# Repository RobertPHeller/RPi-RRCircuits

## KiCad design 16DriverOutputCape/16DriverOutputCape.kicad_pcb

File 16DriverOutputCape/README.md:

# 16DriverOutputCape

This is a MCP23017 with two octal buffers meant to drive 16 LEDs (such as 
signal lamps). No PWM or special effects.  This board is a Cape for a 
BeagleBone Black or Green.  Has address jumpers for the MCP23017 and can be 
stacked -- up to 8 of these capes for up to 128 LEDS -- each board has power 
terminals for the LEDs.

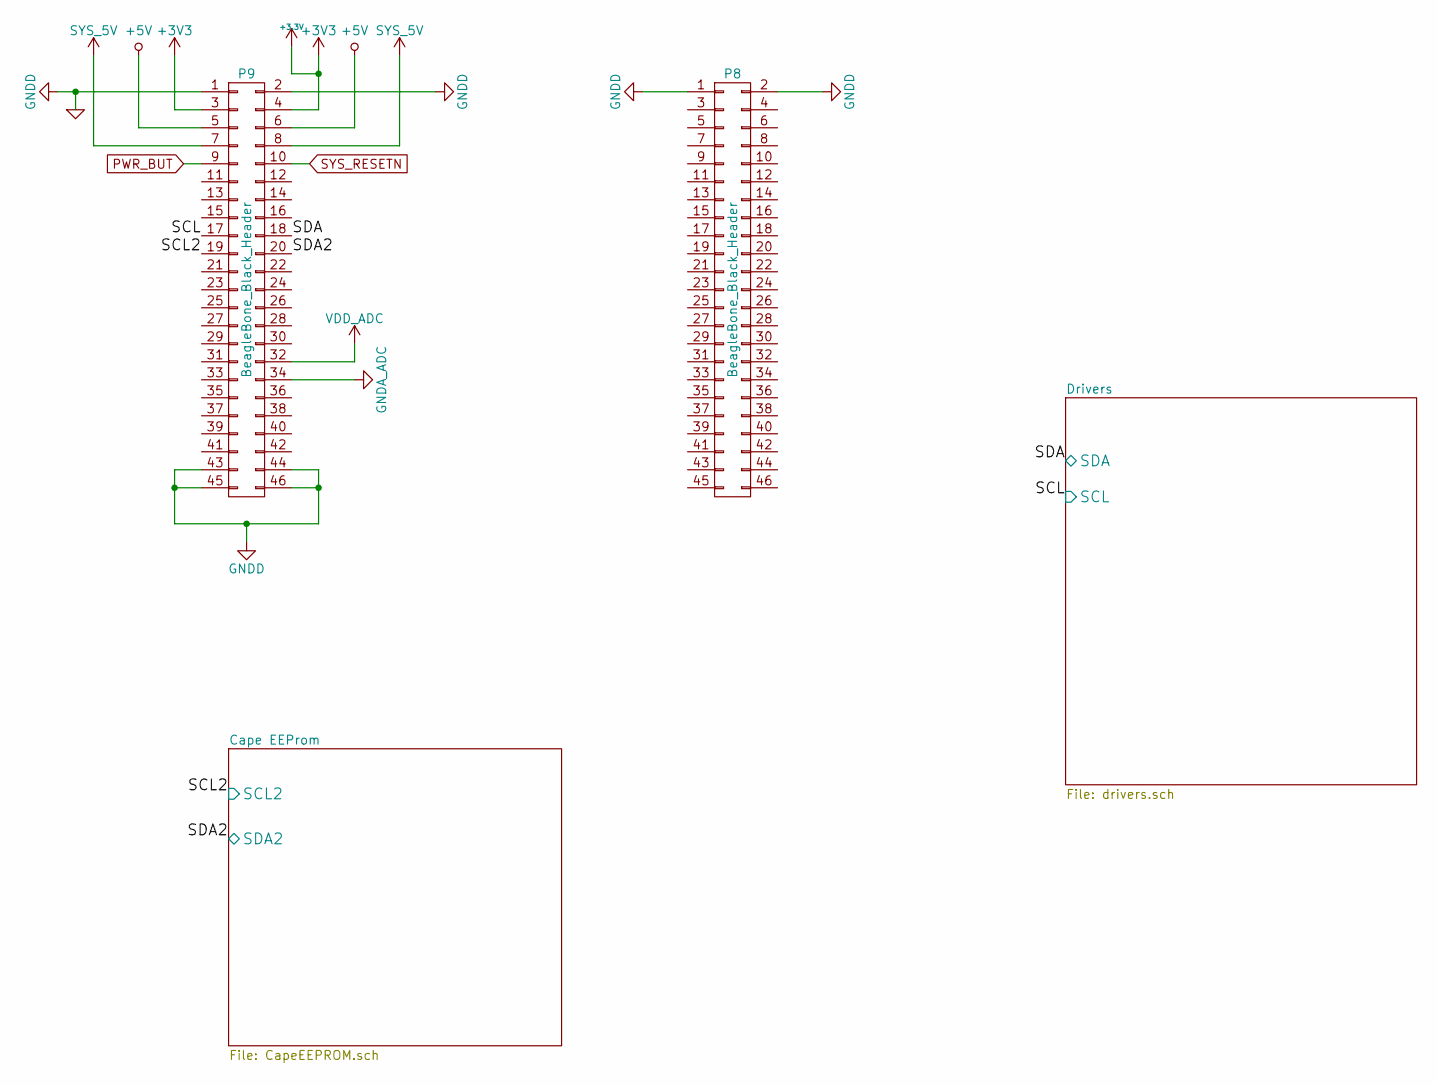
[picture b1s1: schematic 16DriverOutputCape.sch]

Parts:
P8, P9: BeagleBone_Black_Header; Socket_BeagleBone_Black

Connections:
+3.3V: P9.3, P9.4; also elsewhere on the board
+5V: P9.5, P9.6
/Cape EEProm/SCL2: P9.19; also elsewhere on the board
/Cape EEProm/SDA2: P9.20; also elsewhere on the board
/Drivers/SCL: P9.17; also elsewhere on the board
/Drivers/SDA: P9.18; also elsewhere on the board
GND: P8.1, P8.2, P9.1, P9.2, P9.43, P9.44, P9.45, P9.46; also elsewhere on the board
SYS_5V: P9.7, P9.8

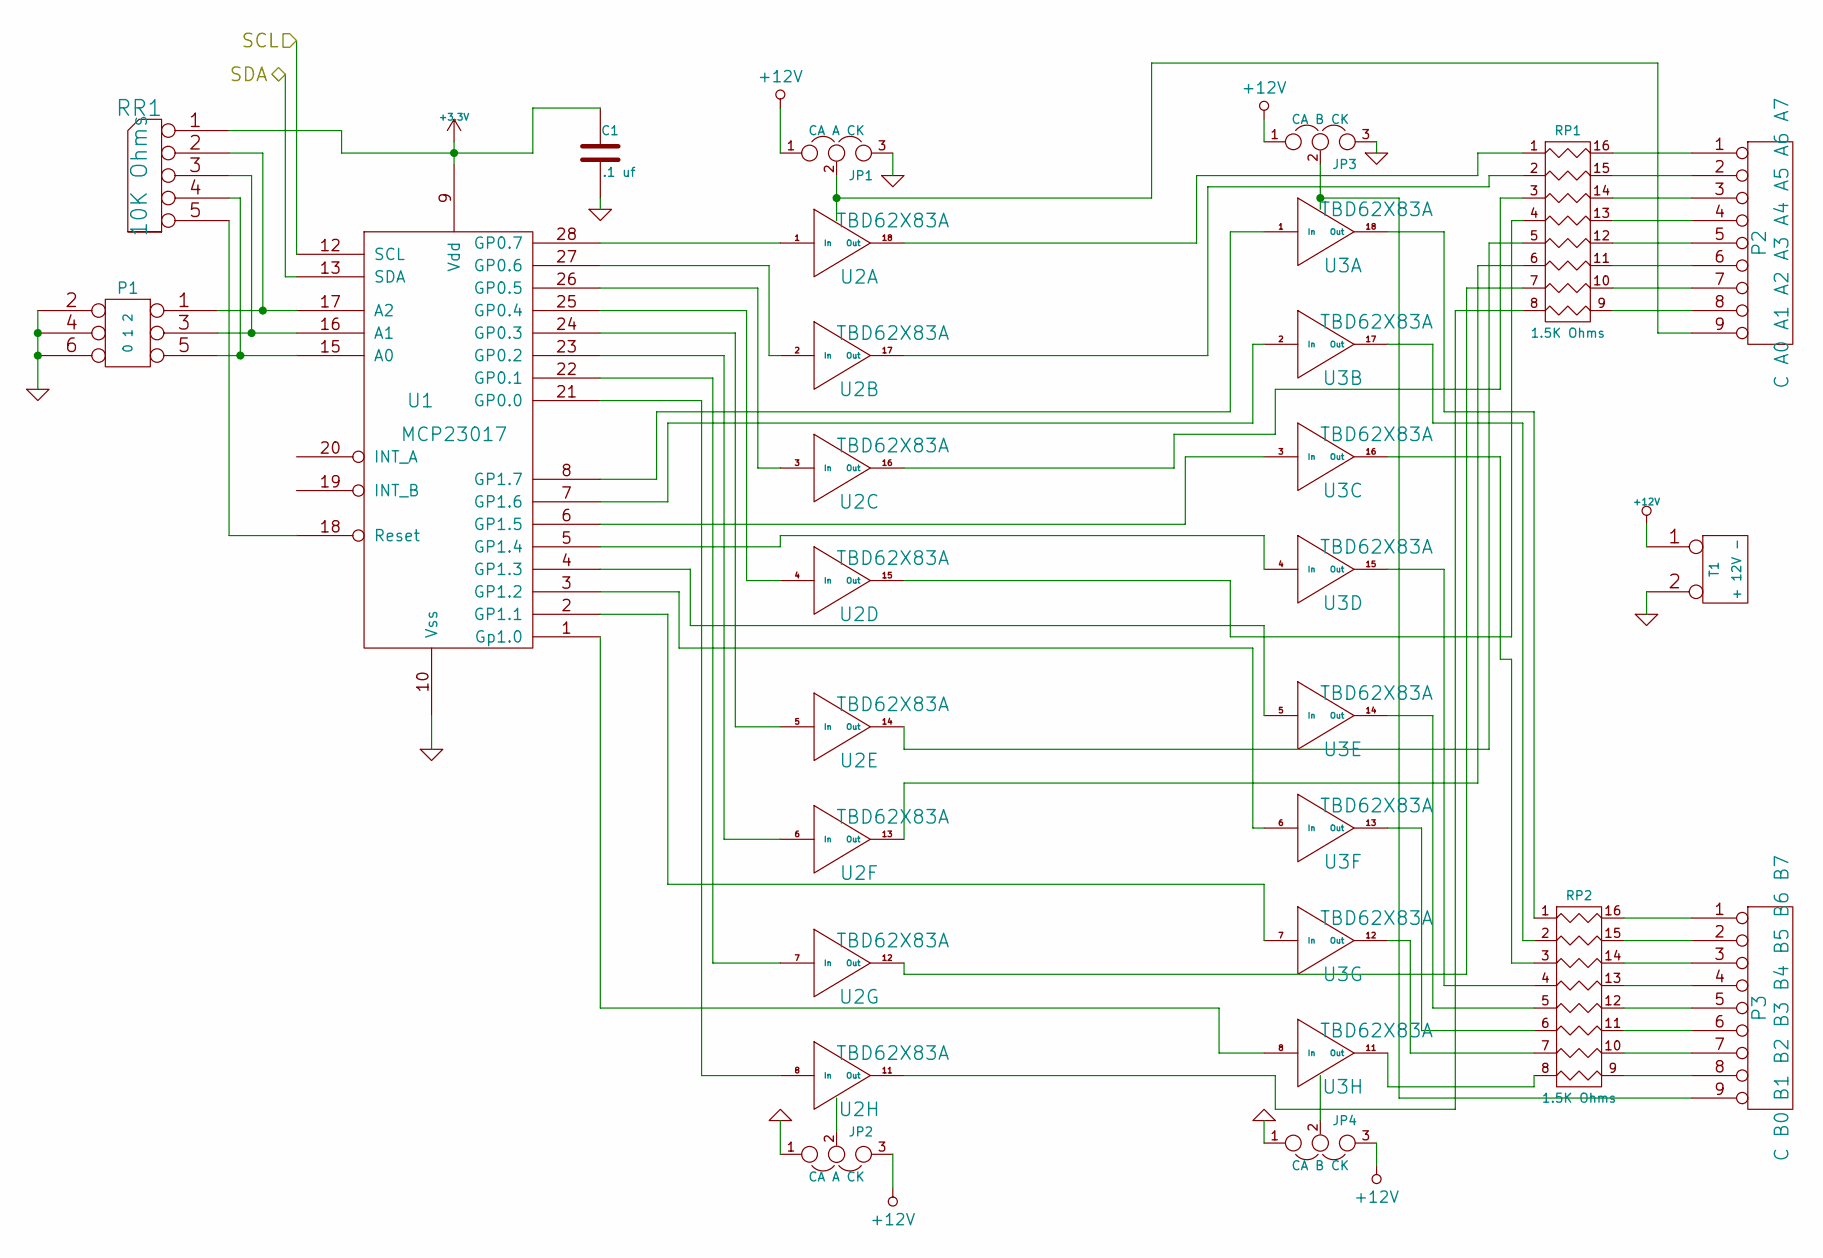
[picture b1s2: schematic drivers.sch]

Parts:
C1: .1 uf
JP1, JP2: CA A CK
JP3, JP4: CA B CK
P1: 0 1 2
P2: C A0 A1 A2 A3 A4 A5 A6 A7
P3: C B0 B1 B2 B3 B4 B5 B6 B7
RP1, RP2: 1.5K Ohms
RR1: 10K Ohms
T1: + 12V -
U1: MCP23017
U2, U3: TBD62X83A

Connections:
+3.3V: C1.1, RR1.1 (COM), U1.9 (Vdd); also elsewhere on the board
+12V: JP1.1, JP2.3, JP3.1, JP4.3, T1.1
/Drivers/SCL: U1.12 (SCL); also elsewhere on the board
/Drivers/SDA: U1.13 (SDA); also elsewhere on the board
GND: C1.2, JP1.3, JP2.1, JP3.3, JP4.1, P1.2, P1.4, P1.6, T1.2 (PM), U1.10 (Vss); also elsewhere on the board
unnamed: P1.1, RR1.2, U1.17 (A2)
unnamed: P1.3, RR1.3, U1.16 (A1)
unnamed: P1.5, RR1.4, U1.15 (A0)
unnamed: RR1.5, U1.18 (Reset)
unnamed: JP2.2, U2.9 (IC)
unnamed: JP3.2, P3.9, U3.10 (OC)
unnamed: JP1.2, P2.9, U2.10 (OC)
unnamed: JP4.2, U3.9 (IC)
unnamed: RP2.6, U3.13 (Out)
unnamed: RP2.8, U3.11 (Out)
unnamed: RP2.7, U3.12 (Out)
unnamed: RP2.5, U3.14 (Out)
unnamed: RP2.4, U3.15 (Out)
unnamed: RP2.3, U3.16 (Out)
unnamed: U1.26 (GP0.5), U2.3 (In)
unnamed: U1.28 (GP0.7), U2.1 (In)
unnamed: U1.27 (GP0.6), U2.2 (In)
unnamed: U1.25 (GP0.4), U2.4 (In)
unnamed: U1.24 (GP0.3), U2.5 (In)
unnamed: RP1.5, U2.14 (Out)
unnamed: U1.23 (GP0.2), U2.6 (In)
unnamed: U1.5 (GP1.4), U3.4 (In)
unnamed: U1.8 (GP1.7), U3.1 (In)
unnamed: U1.22 (GP0.1), U2.7 (In)
unnamed: RP1.7, U2.12 (Out)
unnamed: RP2.1, U3.18 (Out)
unnamed: U1.7 (GP1.6), U3.2 (In)
unnamed: P3.1, RP2.16 (R1)
unnamed: P3.2, RP2.15 (R2)
unnamed: P3.3, RP2.14 (R3)
unnamed: P3.4, RP2.13 (R4)
unnamed: P3.5, RP2.12 (R5)
unnamed: P3.6, RP2.11 (R6)
unnamed: P3.7, RP2.10 (R7)
unnamed: U1.21 (GP0.0), U2.8 (In)
unnamed: P3.8, RP2.9 (R8)
unnamed: U1.1 (Gp1.0), U3.8 (In)
unnamed: U1.2 (GP1.1), U3.7 (In)
unnamed: U1.3 (GP1.2), U3.6 (In)
unnamed: U1.4 (GP1.3), U3.5 (In)
unnamed: P2.6, RP1.11 (R6)
unnamed: RP2.2, U3.17 (Out)
unnamed: P2.1, RP1.16 (R1)
unnamed: P2.2, RP1.15 (R2)
unnamed: P2.3, RP1.14 (R3)
unnamed: P2.4, RP1.13 (R4)
unnamed: P2.5, RP1.12 (R5)
unnamed: P2.7, RP1.10 (R7)
unnamed: P2.8, RP1.9 (R8)
unnamed: RP1.8, U2.11 (Out)
unnamed: RP1.6, U2.13 (Out)
unnamed: RP1.4, U2.15 (Out)
unnamed: RP1.3, U2.16 (Out)
unnamed: RP1.2, U2.17 (Out)
unnamed: RP1.1, U2.18 (Out)
unnamed: U1.6 (GP1.5), U3.3 (In)

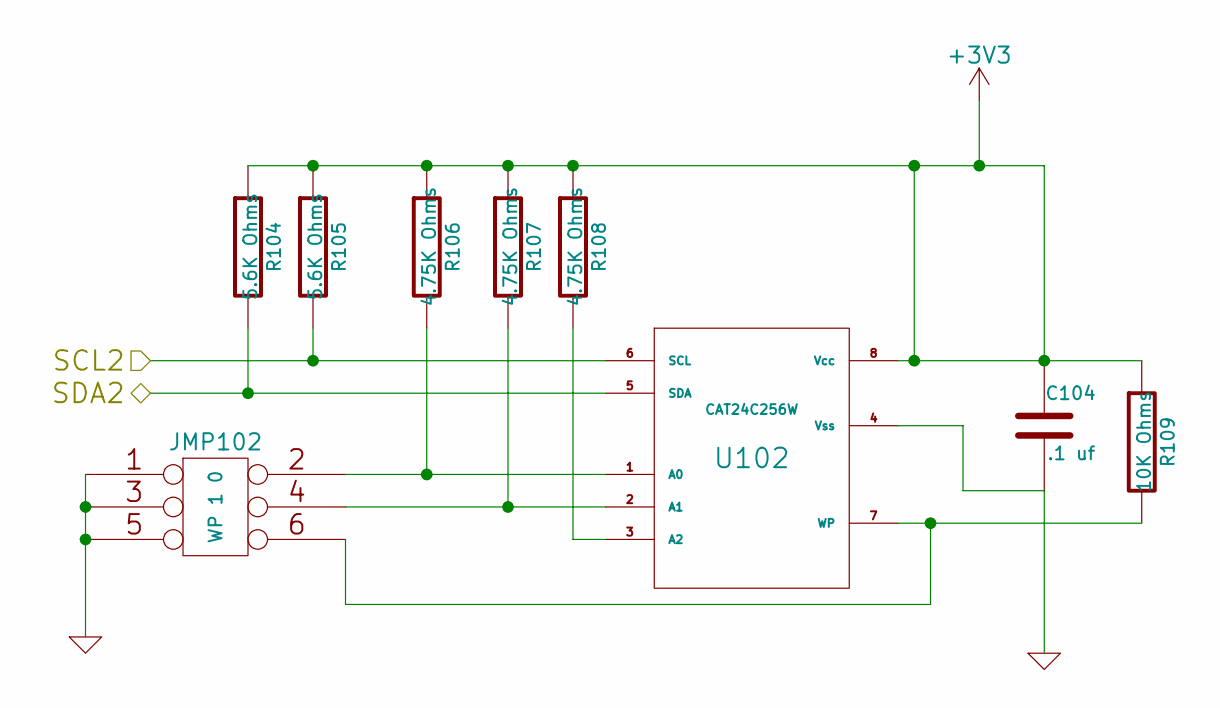
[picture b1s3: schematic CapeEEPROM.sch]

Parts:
C104: .1 uf
JMP102: WP 1 0
R104, R105: 5.6K Ohms
R106, R107, R108: 4.75K Ohms
R109: 10K Ohms
U102: CAT24C256W

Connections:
+3.3V: C104.1, R104.1, R105.1, R106.1, R107.1, R108.1, R109.1, U102.8 (Vcc); also elsewhere on the board
/Cape EEProm/SCL2: R105.2, U102.6 (SCL); also elsewhere on the board
/Cape EEProm/SDA2: R104.2, U102.5 (SDA); also elsewhere on the board
GND: C104.2, JMP102.1, JMP102.3, JMP102.5, U102.4 (Vss); also elsewhere on the board
unnamed: R108.2, U102.3 (A2)
unnamed: JMP102.4, R107.2, U102.2 (A1)
unnamed: JMP102.2, R106.2, U102.1 (A0)
unnamed: JMP102.6, R109.2, U102.7 (WP)

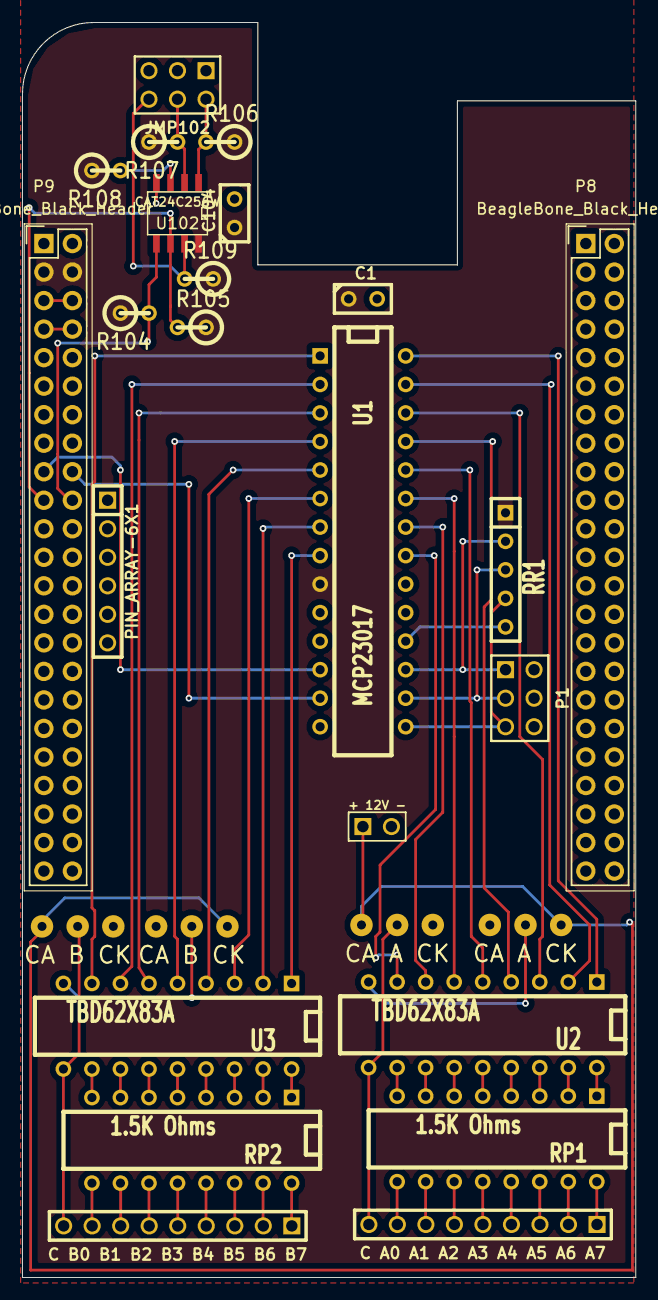
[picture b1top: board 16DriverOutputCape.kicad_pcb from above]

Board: 2 copper layers, 54.6 x 111.8 mm, 27 parts (0 on the bottom side), 69 nets.

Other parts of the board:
PIN_ARRAY-6X1: Val**; PIN_ARRAY-6X1

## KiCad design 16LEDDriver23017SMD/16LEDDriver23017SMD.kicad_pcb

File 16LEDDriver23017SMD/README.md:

# 16LEDDriver23017SMD

This is a SMD variant of 16DriverOutputHAT.

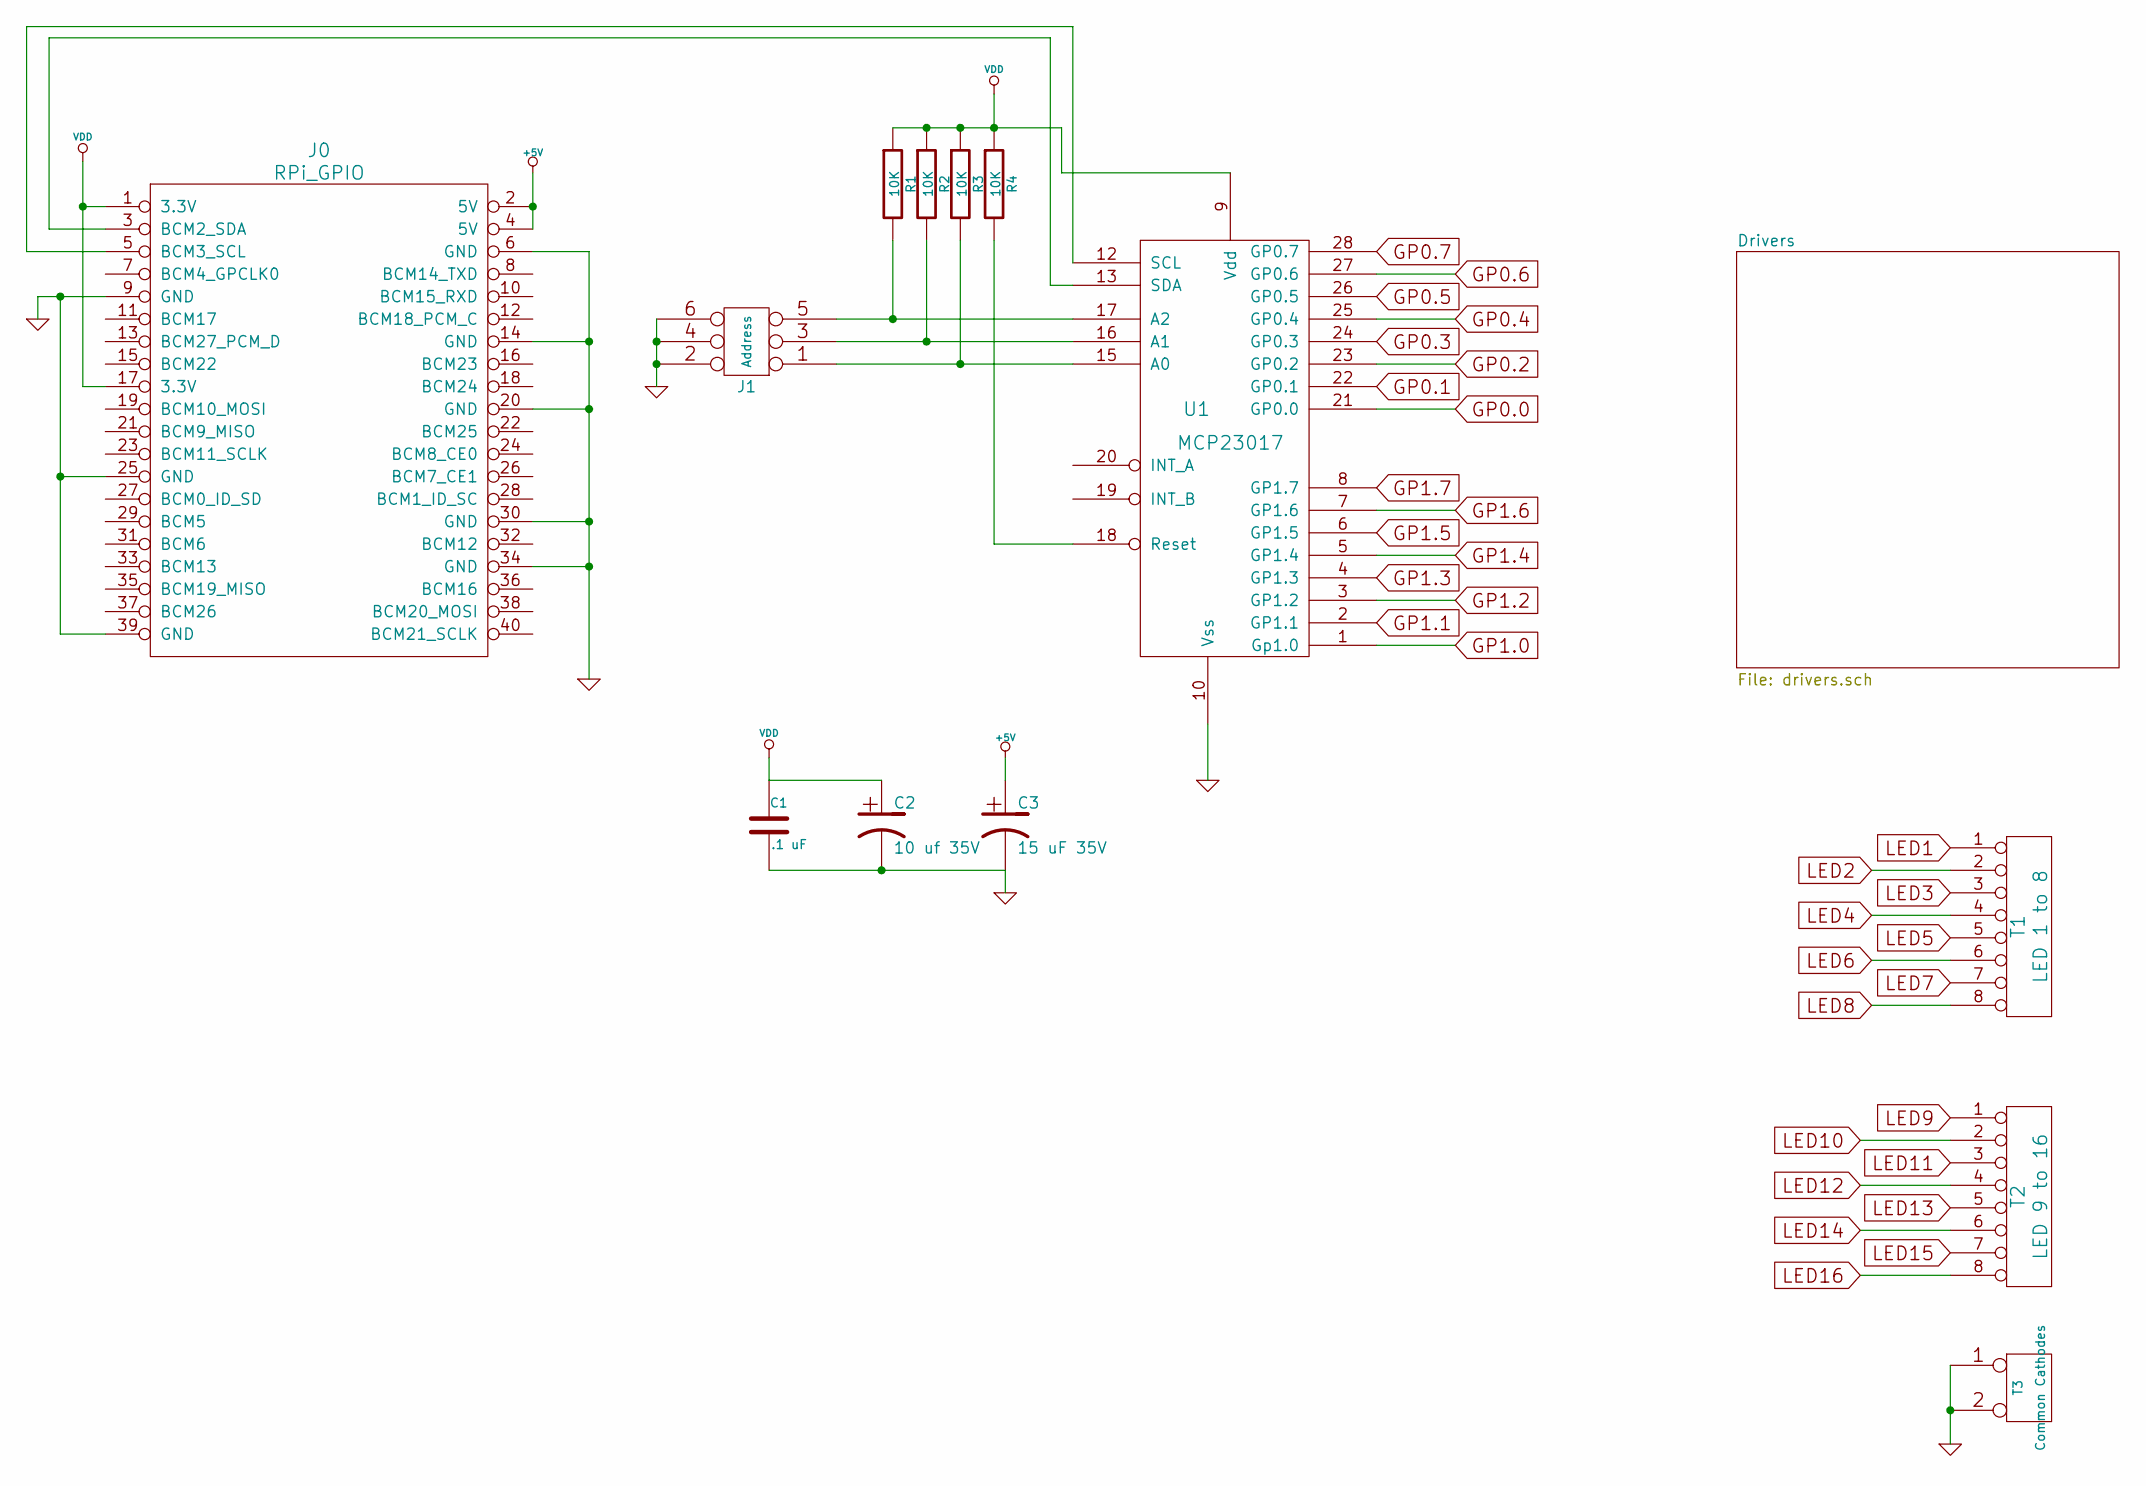
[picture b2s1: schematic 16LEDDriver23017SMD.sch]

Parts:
C1: .1 uF
C2: 10 uf 35V
C3: 15 uF 35V
J0: RPi_GPIO; Samtec_HLE-120-02-XXX-DV-BE-XX-XX
J1: Address; pin_array_3x2
R1, R2, R3, R4: 10K
T1: LED 1 to 8
T2: LED 9 to 16
T3: Common Cathodes
U1: MCP23017; SOIC-28

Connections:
+5V: C3.1, J0.2 (5V), J0.4 (5V); also elsewhere on the board
GND: C1.2, C2.2, C3.2, J0.6 (GND), J0.9 (GND), J0.14 (GND), J0.20 (GND), J0.25 (GND), J0.30 (GND), J0.34 (GND), J0.39 (GND), J1.2, J1.4, J1.6, T3.1, T3.2 (PM), U1.10 (Vss); also elsewhere on the board
GP0.0: U1.21 (GP0.0); also elsewhere on the board
GP0.1: U1.22 (GP0.1); also elsewhere on the board
GP0.2: U1.23 (GP0.2); also elsewhere on the board
GP0.3: U1.24 (GP0.3); also elsewhere on the board
GP0.4: U1.25 (GP0.4); also elsewhere on the board
GP0.5: U1.26 (GP0.5); also elsewhere on the board
GP0.6: U1.27 (GP0.6); also elsewhere on the board
GP0.7: U1.28 (GP0.7); also elsewhere on the board
GP1.0: U1.1 (Gp1.0); also elsewhere on the board
GP1.1: U1.2 (GP1.1); also elsewhere on the board
GP1.2: U1.3 (GP1.2); also elsewhere on the board
GP1.3: U1.4 (GP1.3); also elsewhere on the board
GP1.4: U1.5 (GP1.4); also elsewhere on the board
GP1.5: U1.6 (GP1.5); also elsewhere on the board
GP1.6: U1.7 (GP1.6); also elsewhere on the board
GP1.7: U1.8 (GP1.7); also elsewhere on the board
LED1: T1.1; also elsewhere on the board
LED2: T1.2; also elsewhere on the board
LED3: T1.3; also elsewhere on the board
LED4: T1.4; also elsewhere on the board
LED5: T1.5; also elsewhere on the board
LED6: T1.6; also elsewhere on the board
LED7: T1.7; also elsewhere on the board
LED8: T1.8; also elsewhere on the board
LED9: T2.1; also elsewhere on the board
LED10: T2.2; also elsewhere on the board
LED11: T2.3; also elsewhere on the board
LED12: T2.4; also elsewhere on the board
LED13: T2.5; also elsewhere on the board
LED14: T2.6; also elsewhere on the board
LED15: T2.7; also elsewhere on the board
LED16: T2.8; also elsewhere on the board
unnamed: J0.5 (BCM3_SCL), U1.12 (SCL)
unnamed: J0.3 (BCM2_SDA), U1.13 (SDA)
unnamed: J1.5, R1.2, U1.17 (A2)
unnamed: J1.3, R2.2, U1.16 (A1)
unnamed: J1.1, R3.2, U1.15 (A0)
unnamed: R4.2, U1.18 (Reset)
VDD: C1.1, C2.1, J0.1 (3.3V), J0.17 (3.3V), R1.1, R2.1, R3.1, R4.1, U1.9 (Vdd)

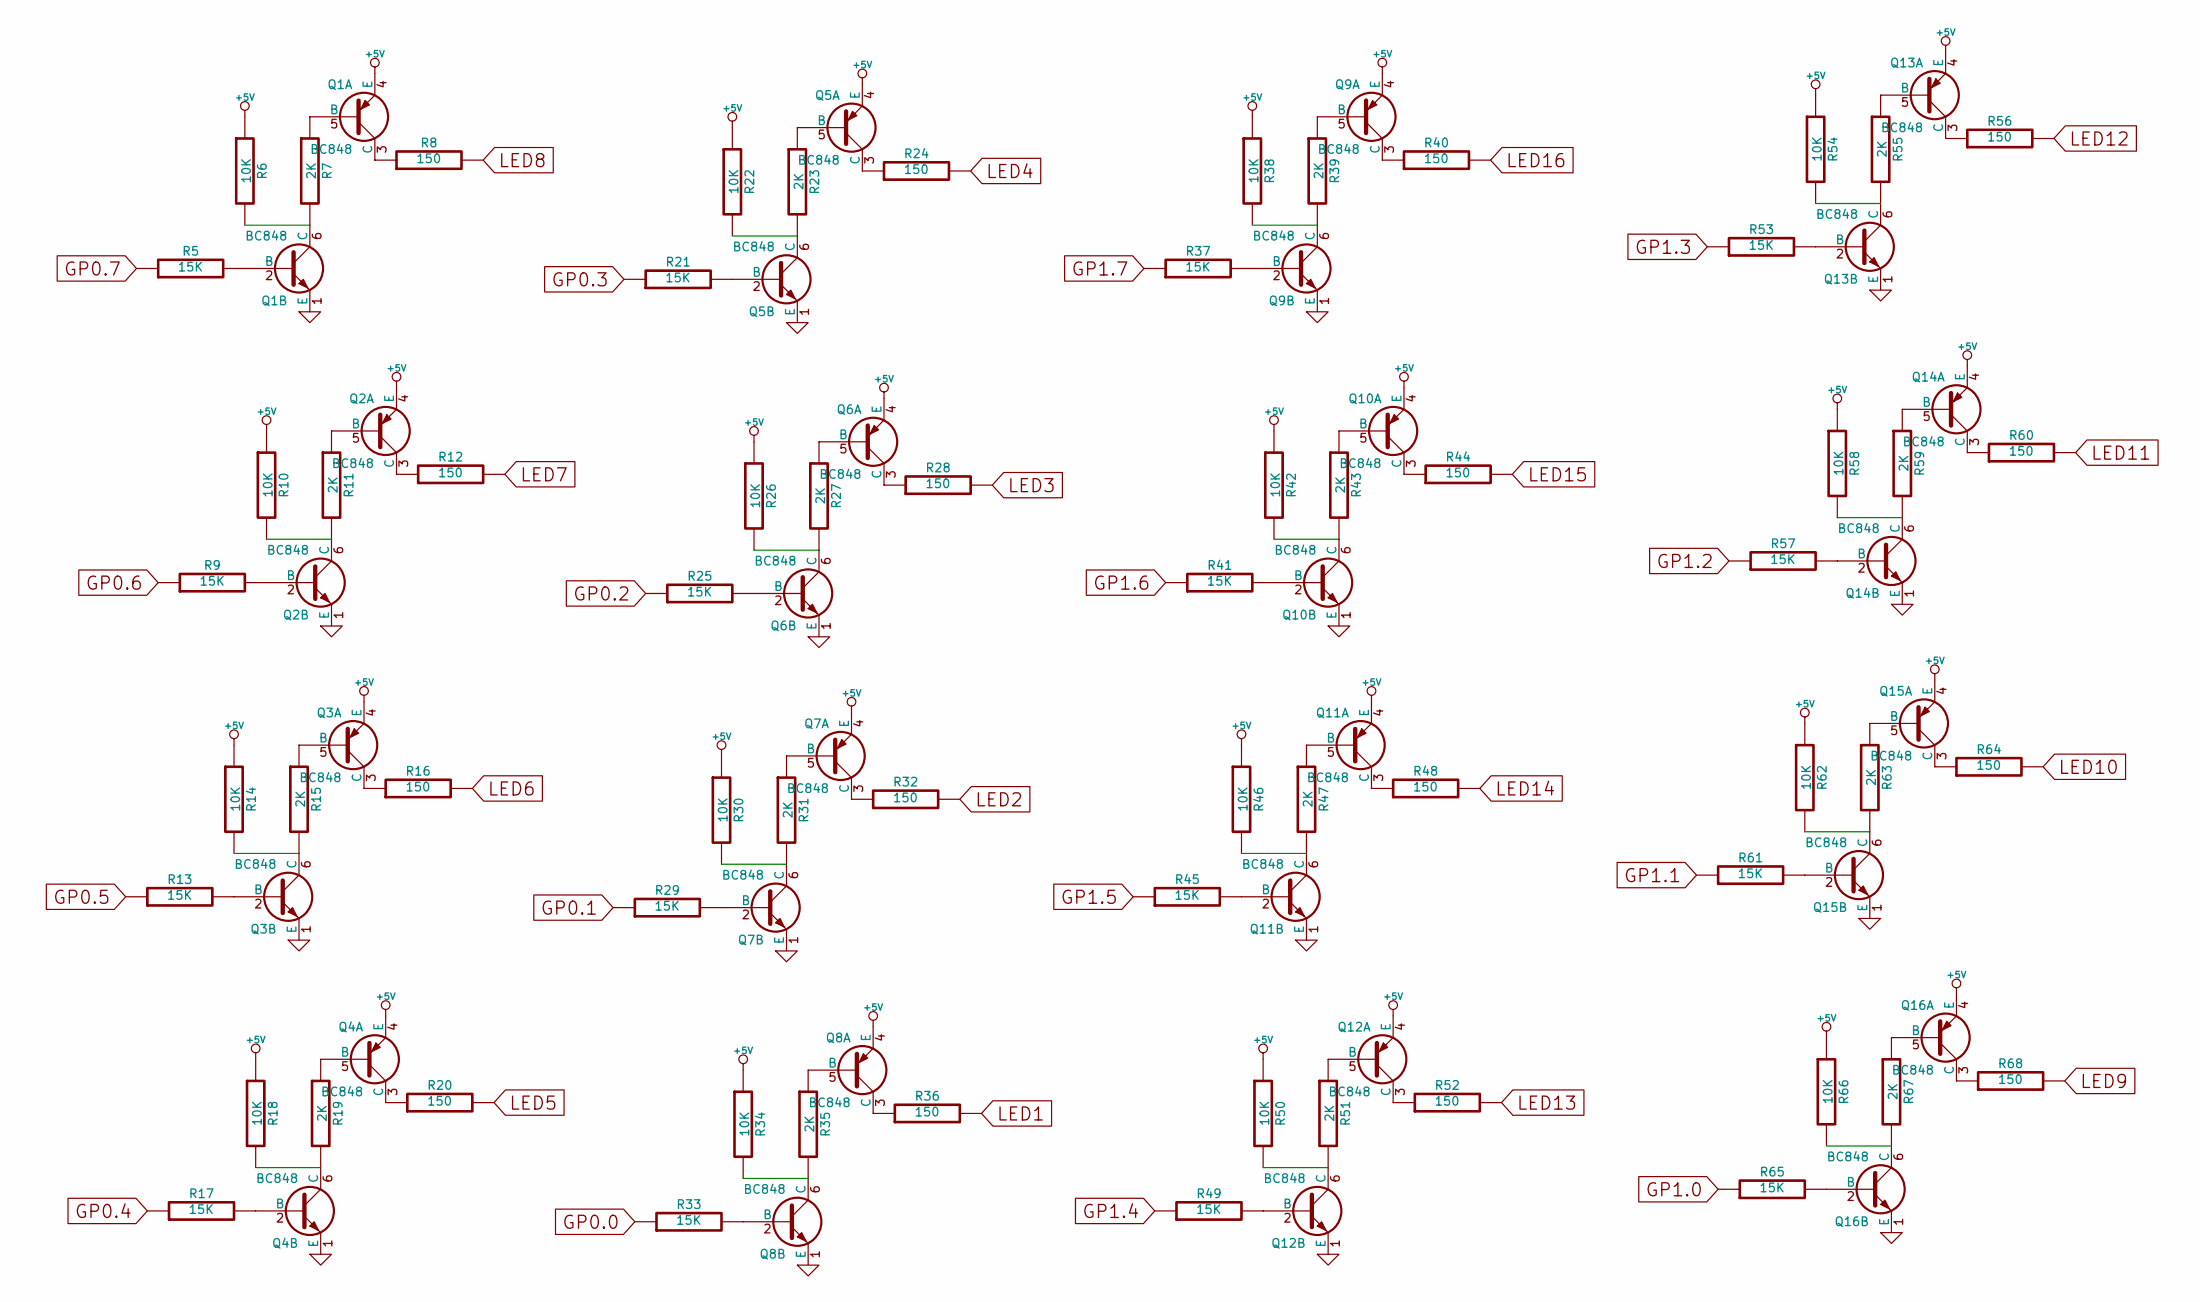
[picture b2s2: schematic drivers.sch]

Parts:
Q1, Q2, Q3, Q4, Q5, Q6, Q7, Q8, Q9, Q10, Q11, Q12, Q13, Q14, Q15, Q16: BC848; SOT-363
R5, R9, R13, R17, R21, R25, R29, R33, R37, R41, R45, R49, R53, R57, R61, R65: 15K
R6, R10, R14, R18, R22, R26, R30, R34, R38, R42, R46, R50, R54, R58, R62, R66: 10K
R7, R11, R15, R19, R23, R27, R31, R35, R39, R43, R47, R51, R55, R59, R63, R67: 2K
R8, R12, R16, R20, R24, R28, R32, R36, R40, R44, R48, R52, R56, R60, R64, R68: 150

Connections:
+5V: Q1.4 (E), Q2.4 (E), Q3.4 (E), Q4.4 (E), Q5.4 (E), Q6.4 (E), Q7.4 (E), Q8.4 (E), Q9.4 (E), Q10.4 (E), Q11.4 (E), Q12.4 (E), Q13.4 (E), Q14.4 (E), Q15.4 (E), Q16.4 (E), R6.1, R10.1, R14.1, R18.1, R22.1, R26.1, R30.1, R34.1, R38.1, R42.1, R46.1, R50.1, R54.1, R58.1, R62.1, R66.1; also elsewhere on the board
GND: Q1.1 (E), Q2.1 (E), Q3.1 (E), Q4.1 (E), Q5.1 (E), Q6.1 (E), Q7.1 (E), Q8.1 (E), Q9.1 (E), Q10.1 (E), Q11.1 (E), Q12.1 (E), Q13.1 (E), Q14.1 (E), Q15.1 (E), Q16.1 (E); also elsewhere on the board
GP0.0: R33.1; also elsewhere on the board
GP0.1: R29.1; also elsewhere on the board
GP0.2: R25.1; also elsewhere on the board
GP0.3: R21.1; also elsewhere on the board
GP0.4: R17.1; also elsewhere on the board
GP0.5: R13.1; also elsewhere on the board
GP0.6: R9.1; also elsewhere on the board
GP0.7: R5.1; also elsewhere on the board
GP1.0: R65.1; also elsewhere on the board
GP1.1: R61.1; also elsewhere on the board
GP1.2: R57.1; also elsewhere on the board
GP1.3: R53.1; also elsewhere on the board
GP1.4: R49.1; also elsewhere on the board
GP1.5: R45.1; also elsewhere on the board
GP1.6: R41.1; also elsewhere on the board
GP1.7: R37.1; also elsewhere on the board
LED1: R36.2; also elsewhere on the board
LED2: R32.2; also elsewhere on the board
LED3: R28.2; also elsewhere on the board
LED4: R24.2; also elsewhere on the board
LED5: R20.2; also elsewhere on the board
LED6: R16.2; also elsewhere on the board
LED7: R12.2; also elsewhere on the board
LED8: R8.2; also elsewhere on the board
LED9: R68.2; also elsewhere on the board
LED10: R64.2; also elsewhere on the board
LED11: R60.2; also elsewhere on the board
LED12: R56.2; also elsewhere on the board
LED13: R52.2; also elsewhere on the board
LED14: R48.2; also elsewhere on the board
LED15: R44.2; also elsewhere on the board
LED16: R40.2; also elsewhere on the board
unnamed: Q11.2 (B), R45.2
unnamed: Q11.5 (B), R47.1
unnamed: Q11.3 (C), R48.1
unnamed: Q10.3 (C), R44.1
unnamed: Q10.2 (B), R41.2
unnamed: Q10.6 (C), R42.2, R43.2
unnamed: Q10.5 (B), R43.1
unnamed: Q12.3 (C), R52.1
unnamed: Q12.2 (B), R49.2
unnamed: Q12.6 (C), R50.2, R51.2
unnamed: Q12.5 (B), R51.1
unnamed: Q11.6 (C), R46.2, R47.2
unnamed: Q8.6 (C), R34.2, R35.2
unnamed: Q7.6 (C), R30.2, R31.2
unnamed: Q6.6 (C), R26.2, R27.2
unnamed: Q16.6 (C), R66.2, R67.2
unnamed: Q15.6 (C), R62.2, R63.2
unnamed: Q14.6 (C), R58.2, R59.2
unnamed: Q13.6 (C), R54.2, R55.2
unnamed: Q9.6 (C), R38.2, R39.2
unnamed: Q5.6 (C), R22.2, R23.2
unnamed: Q4.6 (C), R18.2, R19.2
unnamed: Q3.6 (C), R14.2, R15.2
unnamed: Q2.6 (C), R10.2, R11.2
unnamed: Q1.6 (C), R6.2, R7.2
unnamed: Q5.3 (C), R24.1
unnamed: Q5.2 (B), R21.2
unnamed: Q5.5 (B), R23.1
unnamed: Q4.3 (C), R20.1
unnamed: Q4.2 (B), R17.2
unnamed: Q4.5 (B), R19.1
unnamed: Q7.5 (B), R31.1
unnamed: Q7.2 (B), R29.2
unnamed: Q7.3 (C), R32.1
unnamed: Q6.3 (C), R28.1
unnamed: Q6.2 (B), R25.2
unnamed: Q6.5 (B), R27.1
unnamed: Q2.5 (B), R11.1
unnamed: Q2.2 (B), R9.2
unnamed: Q2.3 (C), R12.1
unnamed: Q1.3 (C), R8.1
unnamed: Q1.2 (B), R5.2
unnamed: Q1.5 (B), R7.1
unnamed: Q3.3 (C), R16.1
unnamed: Q3.2 (B), R13.2
unnamed: Q3.5 (B), R15.1
unnamed: Q16.5 (B), R67.1
unnamed: Q16.2 (B), R65.2
unnamed: Q16.3 (C), R68.1
unnamed: Q15.3 (C), R64.1
unnamed: Q15.2 (B), R61.2
unnamed: Q15.5 (B), R63.1
unnamed: Q14.3 (C), R60.1
unnamed: Q9.3 (C), R40.1
unnamed: Q9.2 (B), R37.2
unnamed: Q9.5 (B), R39.1
unnamed: Q13.5 (B), R55.1
unnamed: Q13.3 (C), R56.1
unnamed: Q8.3 (C), R36.1
unnamed: Q8.2 (B), R33.2
unnamed: Q8.5 (B), R35.1
unnamed: Q14.2 (B), R57.2
unnamed: Q14.5 (B), R59.1
unnamed: Q13.2 (B), R53.2

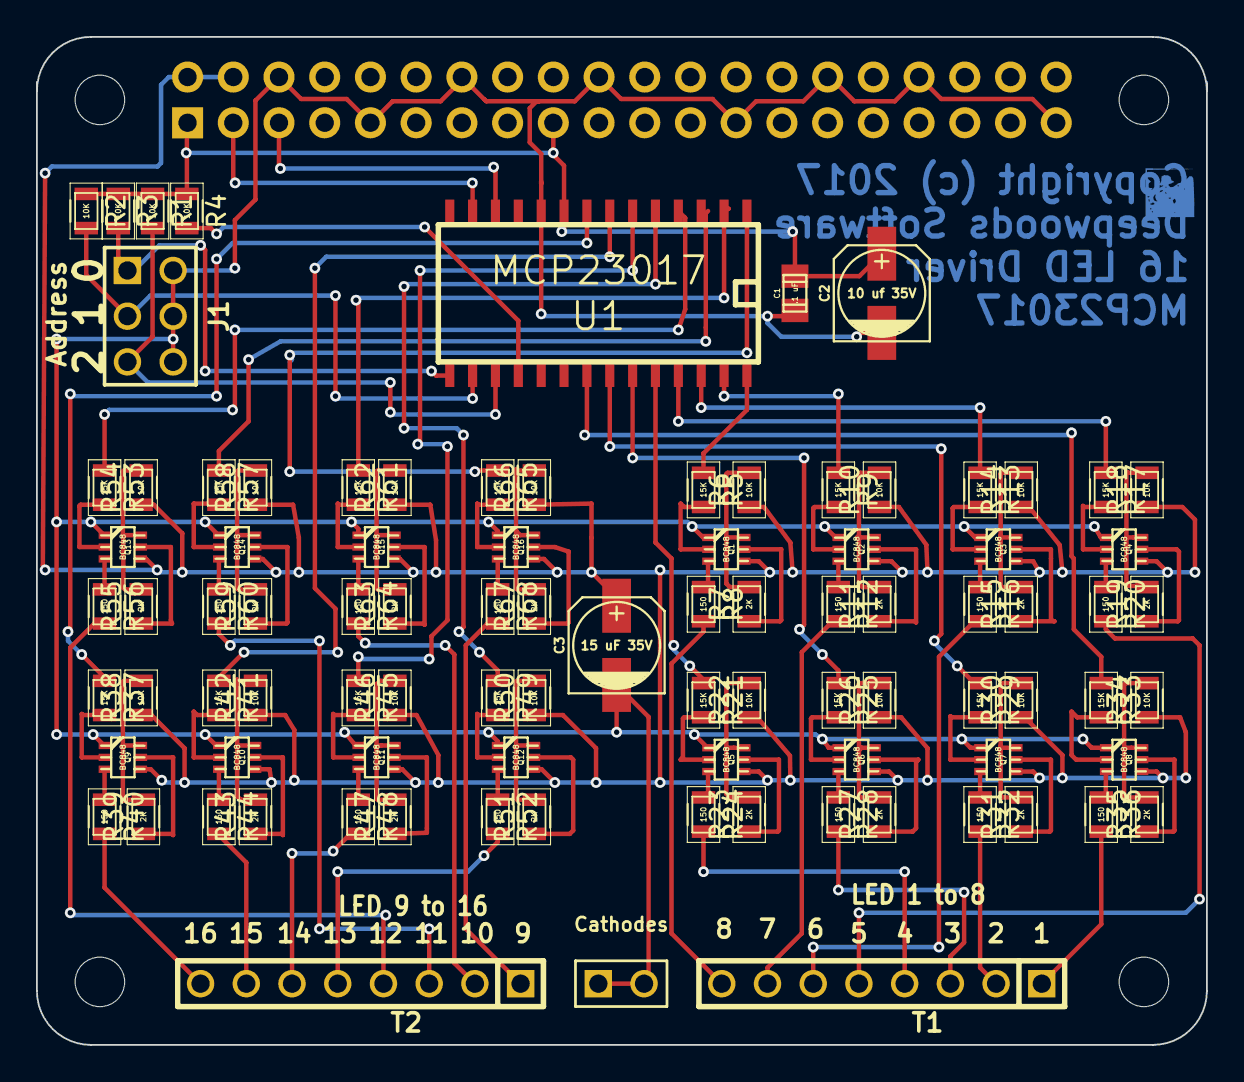
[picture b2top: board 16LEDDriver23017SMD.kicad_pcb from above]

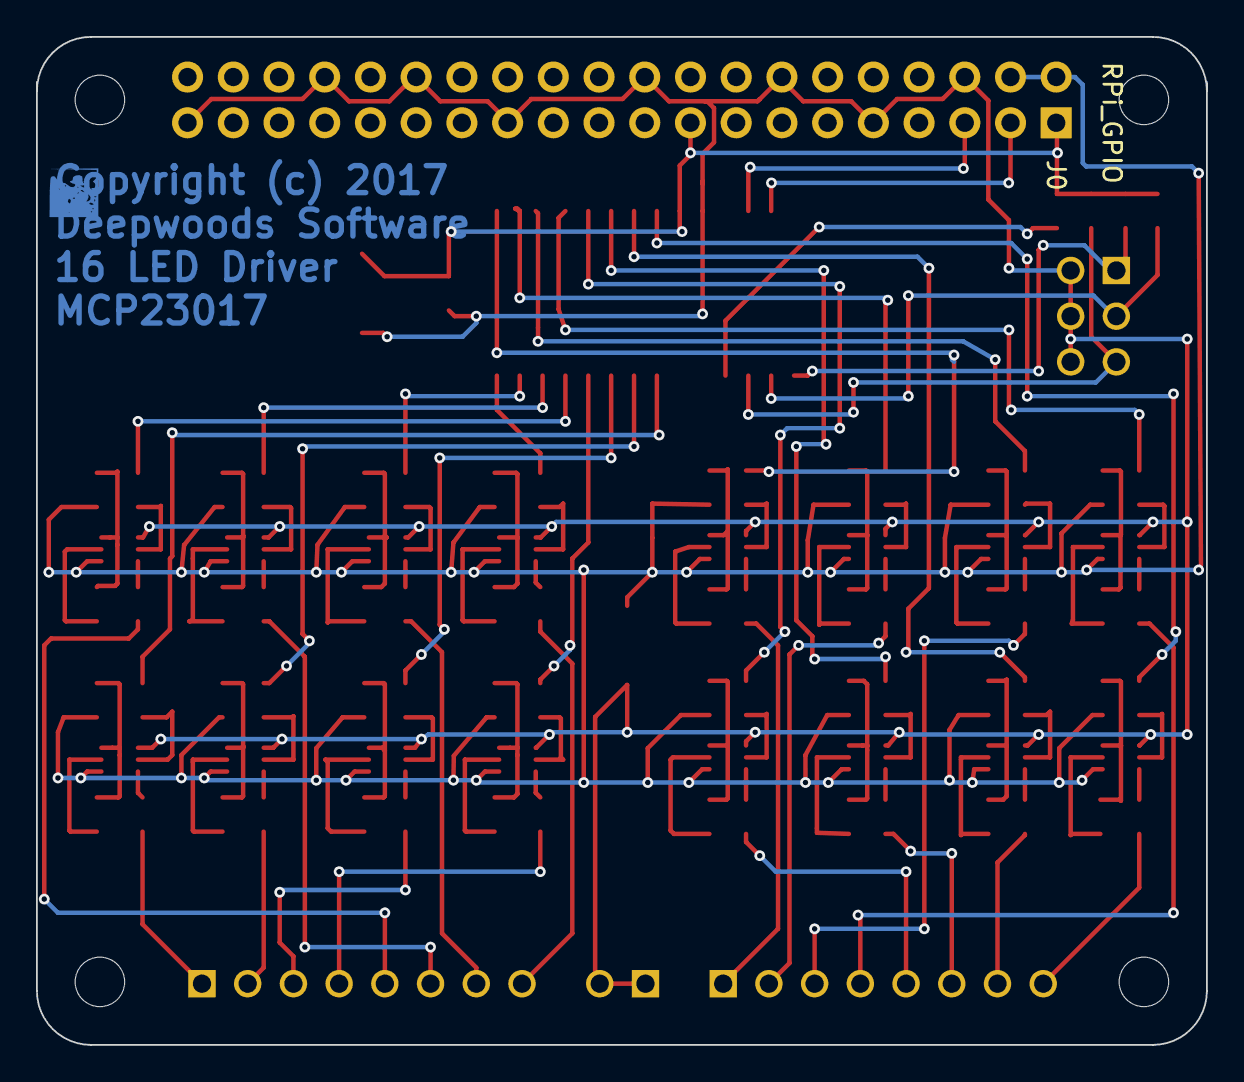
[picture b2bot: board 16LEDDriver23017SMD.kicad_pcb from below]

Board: 2 copper layers, 65.0 x 56.0 mm, 97 parts (5 on the bottom side), 105 nets.

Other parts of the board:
H1, H2, H3, H4: RPi_Hat_Mounting_Hole

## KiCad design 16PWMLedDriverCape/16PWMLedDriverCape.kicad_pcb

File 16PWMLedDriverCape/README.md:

# 16PWMLedDriverCape

This is a PCA9685 with two octal buffers meant to drive 16 LEDs (such as 
signal lamps).  This board is much like 16DriverOutputHat, but uses a PWM chip 
to allow for special effects and allows for brightness adjustment.  Has 
address jumpers for the PCA9685 and can be stacked -- up to 64 boards (WOW) 
for up to 1024 LEDs (WOW) -- each board has power terminals for the LEDs.

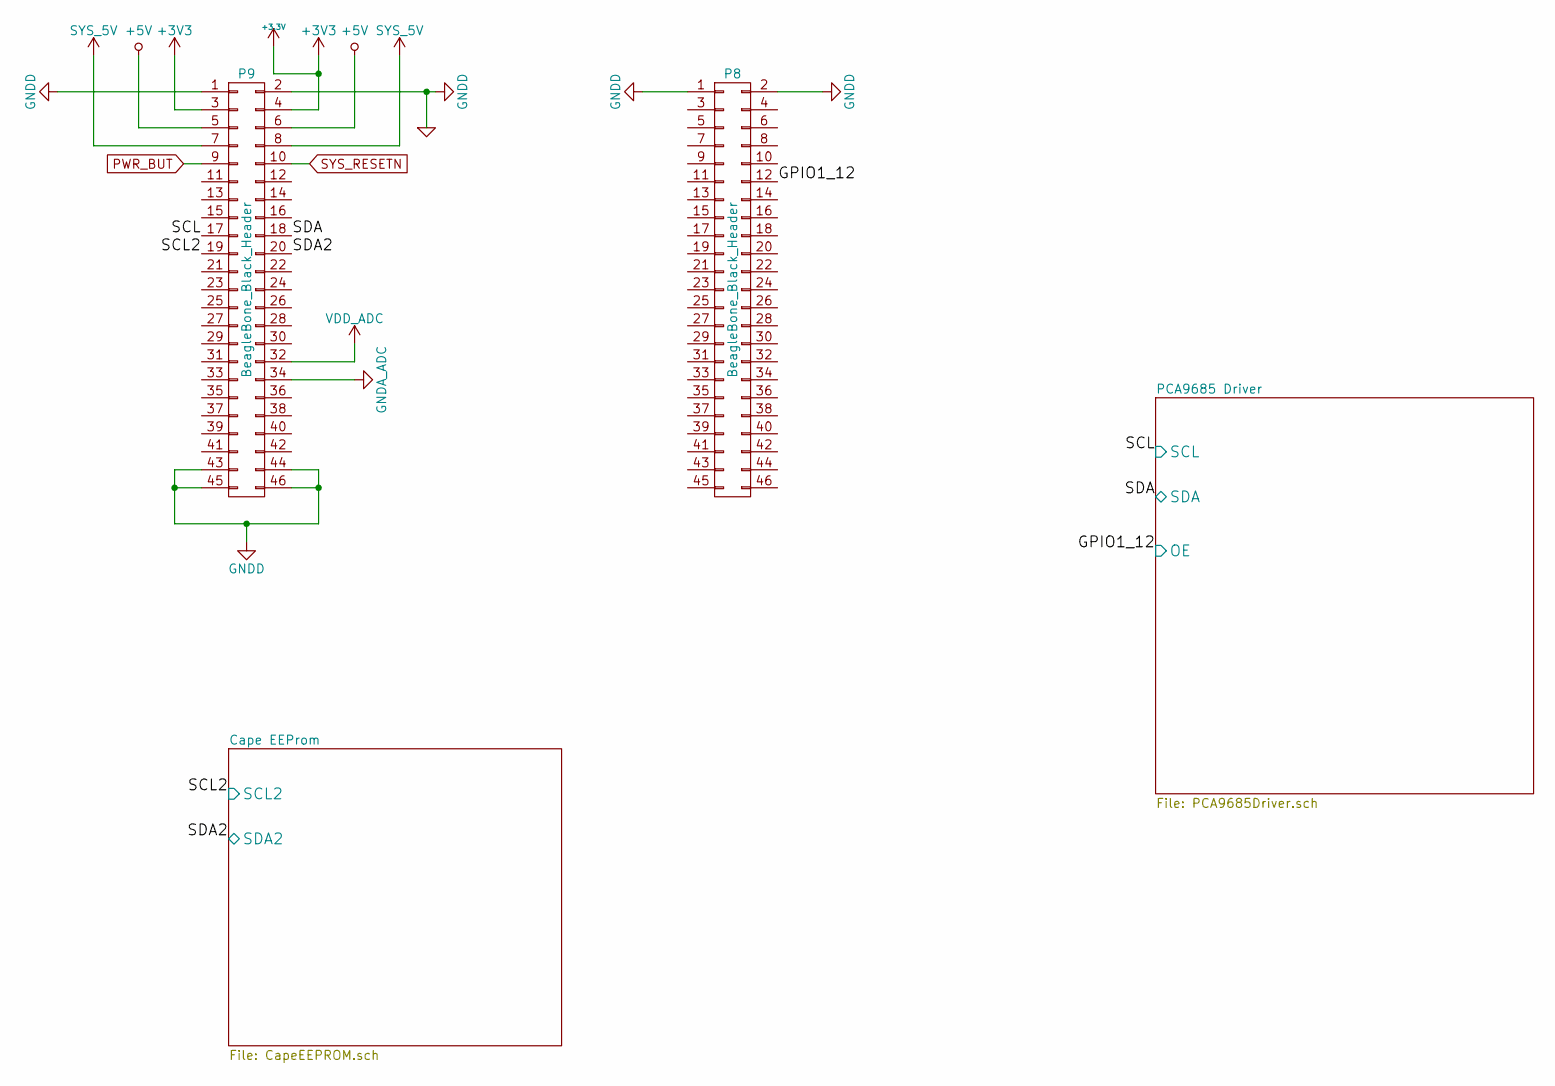
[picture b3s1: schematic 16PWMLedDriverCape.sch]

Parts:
P8, P9: BeagleBone_Black_Header; Socket_BeagleBone_Black

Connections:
+3.3V: P9.3, P9.4; also elsewhere on the board
+5V: P9.5, P9.6
/Cape EEProm/SCL2: P9.19; also elsewhere on the board
/Cape EEProm/SDA2: P9.20; also elsewhere on the board
/PCA9685 Driver/OE: P8.12; also elsewhere on the board
/PCA9685 Driver/SCL: P9.17; also elsewhere on the board
/PCA9685 Driver/SDA: P9.18; also elsewhere on the board
GND: P8.1, P8.2, P9.1, P9.2, P9.43, P9.44, P9.45, P9.46; also elsewhere on the board
SYS_5V: P9.7, P9.8

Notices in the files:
16LEDDriver23017SMD/16LEDDriver23017SMD.kicad_pcb:
Copyright (c) 2017
